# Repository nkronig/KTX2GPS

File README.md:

# KTX2GPS
Extracts the Position data from Flarm signal

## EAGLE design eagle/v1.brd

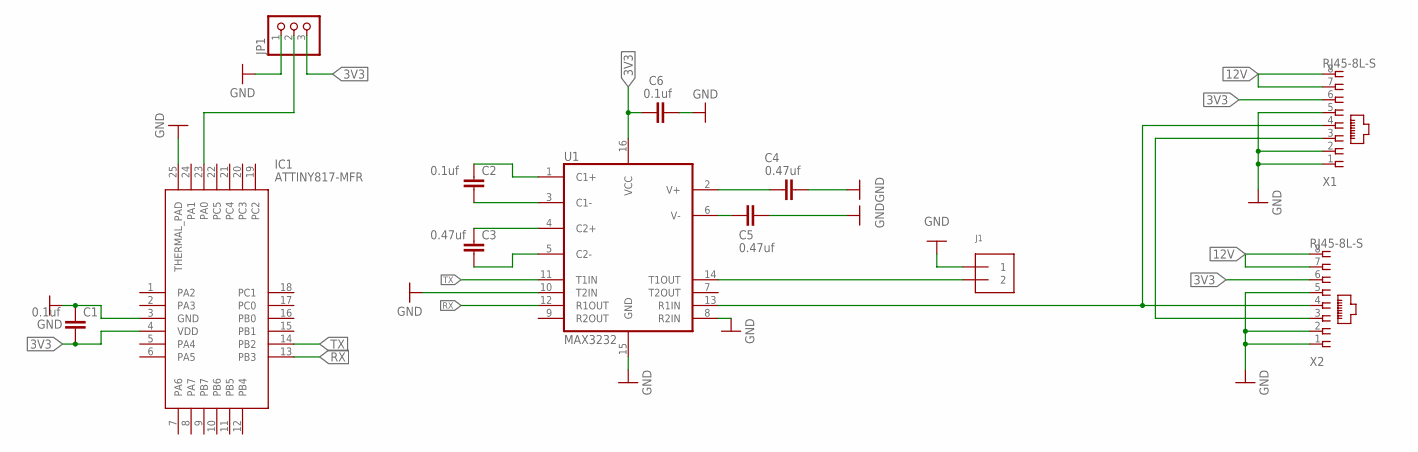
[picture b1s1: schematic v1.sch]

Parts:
C1, C2, C6: 0.1uf; C0805
C3, C4, C5: 0.47uf; C0805
IC1: ATTINY817-MFR; QFN50P400X400X90-25N
J1: TERMBLOCK_1X2; TERMBLOCK_1X2-3.5MM
JP1: PINHD-1X3; 1X03
U1: MAX3232; SO16
X1, X2: RJ45-8L-S; RJ45-NO-SHIELD

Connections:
3V3: C1.2, C6.2, IC1.4 (VDD), JP1.3, U1.16 (VCC), X1.6, X2.6
12V: X1.7, X1.8, X2.7, X2.8
GND: C1.1, C4.1, C5.1, C6.1, IC1.3 (GND), IC1.25 (THERMAL_PAD), J1.1, JP1.1, U1.8 (R2IN), U1.10 (T2IN), U1.15 (GND), X1.1, X1.2, X1.5, X2.1, X2.2, X2.5
unnamed: X1.3, X2.3
unnamed: J1.2, U1.14 (T1OUT)
unnamed: IC1.23 (PA0), JP1.2
unnamed: C2.1, U1.1 (C1+)
unnamed: C2.2, U1.3 (C1-)
unnamed: C3.1, U1.4 (C2+)
unnamed: C3.2, U1.5 (C2-)
unnamed: C4.2, U1.2 (V+)
unnamed: C5.2, U1.6 (V-)
unnamed: U1.13 (R1IN), X1.4, X2.4
RX: IC1.13 (PB3), U1.12 (R1OUT)
TX: IC1.14 (PB2), U1.11 (T1IN)

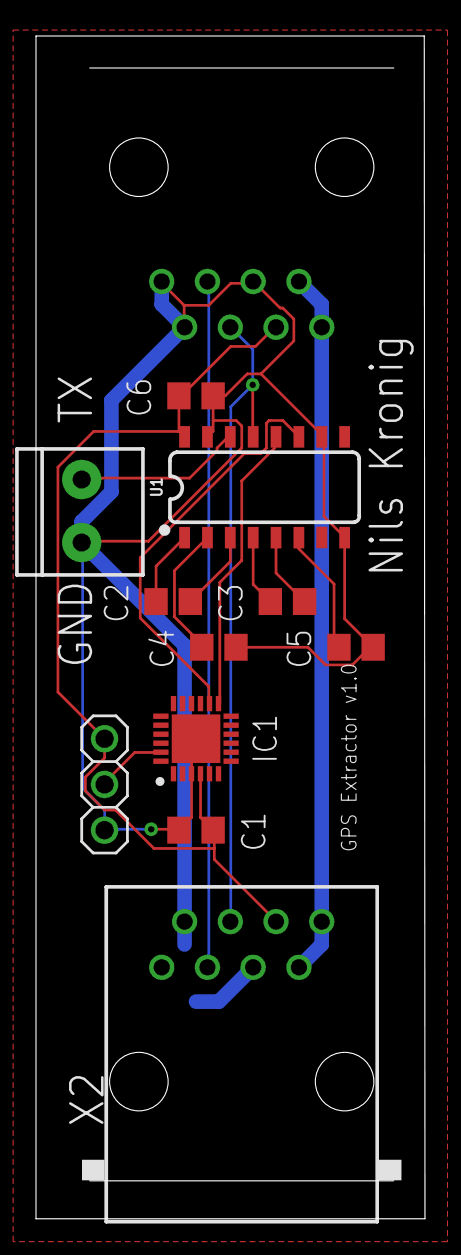
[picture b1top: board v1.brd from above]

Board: 2 copper layers, 21.6 x 65.7 mm, 12 parts (1 on the bottom side), 15 nets.

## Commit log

2021-11-11 Inital commit
2021-11-11 Filter funktioniert
2024-12-27 final
2025-04-28 234657utcikvuzhlj

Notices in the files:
parts and their libraries:
SparkFun-IC-Comms: Licensing: Creative Commons ShareAlike 4.0 International - https://creativecommons.org/licenses/by-sa/4.0
microbuilder: This work is placed in the public domain, and may be freely used for commercial and non-commercial work with the following conditions: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
